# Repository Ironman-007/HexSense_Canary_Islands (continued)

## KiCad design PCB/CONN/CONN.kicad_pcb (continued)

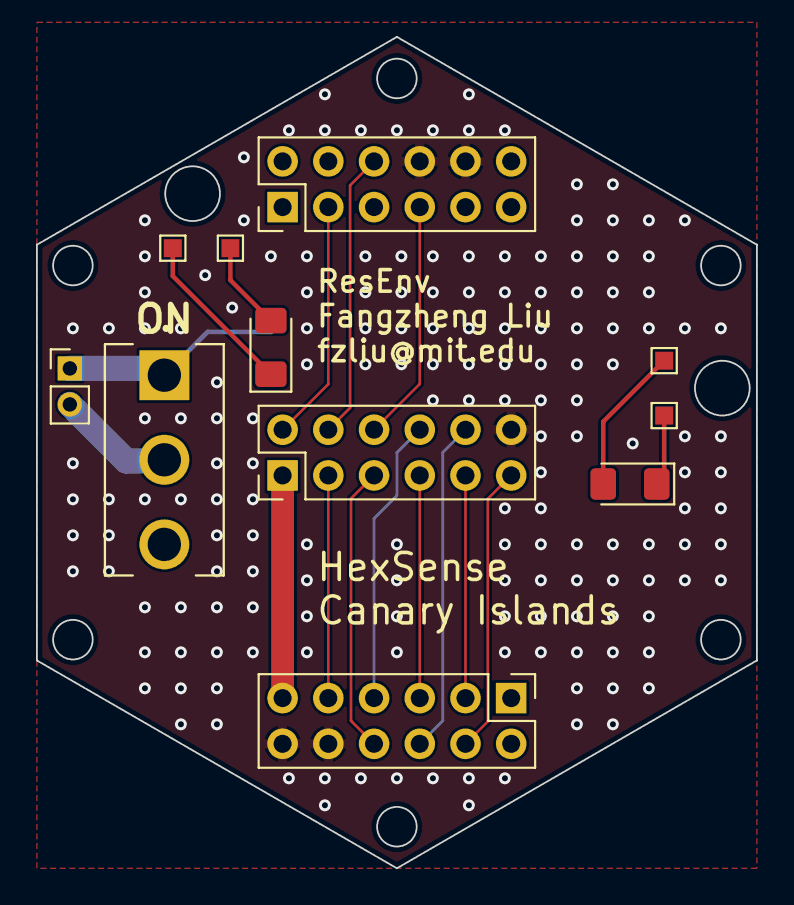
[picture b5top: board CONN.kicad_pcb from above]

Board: 2 copper layers, 40.0 x 46.2 mm, 12 parts (1 on the bottom side), 18 nets.

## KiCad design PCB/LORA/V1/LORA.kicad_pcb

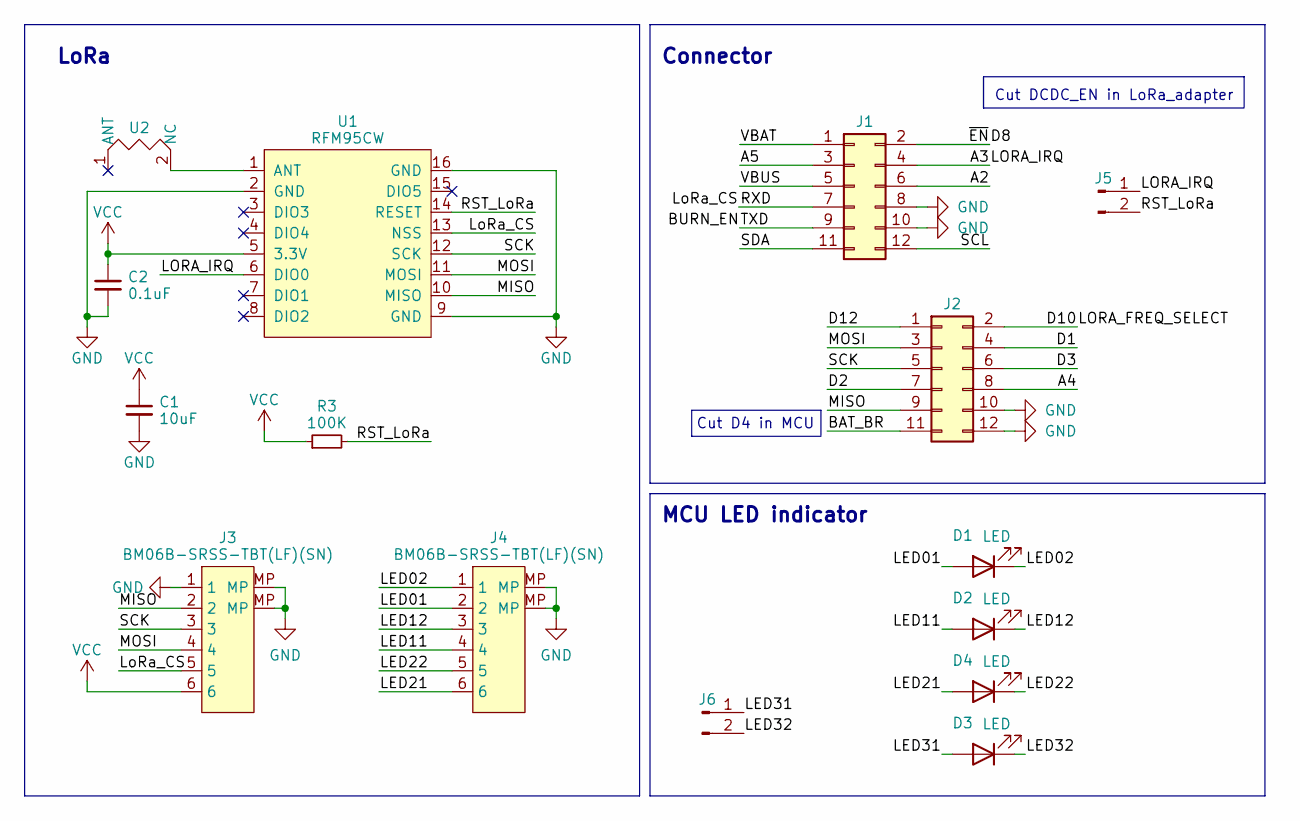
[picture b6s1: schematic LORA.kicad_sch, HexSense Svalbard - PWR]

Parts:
C1: 10uF; C_1206_3216Metric_Pad1.33x1.80mm_HandSolder
C2: 0.1uF; C_1206_3216Metric_Pad1.33x1.80mm_HandSolder
D1, D2, D3, D4: LED; LED_0603_1608Metric_Pad1.05x0.95mm_HandSolder
J1, J2: Conn_02x06_Odd_Even; PinHeader_2x06_P2.54mm_Vertical
J3, J4: BM06B-SRSS-TBT(LF)(SN); JST_SH_BM06B-SRSS-TB_1x06-1MP_P1.00mm_Vertical
J5, J6: Conn_01x02_Pin; PinHeader_1x02_P2.00mm_Vertical
R3: 100K; R_0603_1608Metric_Pad0.98x0.95mm_HandSolder
U1: RFM95CW; XCVR_RFM95W-915S2
U2: ANT-916-HESM

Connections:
/A2: J1.6
/A3: J1.4, J5.1, U1.6 (DIO0)
/A4: J2.8
/A5: J1.3
/BAT_BR: J2.11
/BURN_EN: J1.9
/D1: J2.4
/D2: J2.7
/D3: J2.6
/D8: J1.2
/D10: J2.2
/D12: J2.1
/LED01: D1.2 (A), J4.2
/LED02: D1.1 (K), J4.1
/LED11: D2.2 (A), J4.4
/LED12: D2.1 (K), J4.3
/LED21: D4.2 (A), J4.6
/LED22: D4.1 (K), J4.5
/LED31: D3.2 (A), J6.1
/LED32: D3.1 (K), J6.2
/LoRa_CS: J1.7, J3.5, U1.13 (NSS)
/MISO: J2.9, J3.2, U1.10 (MISO)
/MOSI: J2.3, J3.4, U1.11 (MOSI)
/RST_LoRa: J5.2, R3.2, U1.14 (RESET)
/SCK: J2.5, J3.3, U1.12 (SCK)
/SCL: J1.12
/SDA: J1.11
/VBAT: J1.1
/VBUS: J1.5
GND: C1.2, C2.2, J1.8, J1.10, J2.10, J2.12, J3.1, J3.MP, J4.MP, U1.2 (GND), U1.9 (GND), U1.16 (GND)
unnamed: U1.1 (ANT), U2.2 (NC)
VCC: C1.1, C2.1, J3.6, R3.1, U1.5 (3.3V)

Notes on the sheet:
Cut D4 in MCU
LoRa
Connector
MCU LED indicator
Cut DCDC_EN in LoRa_adapter

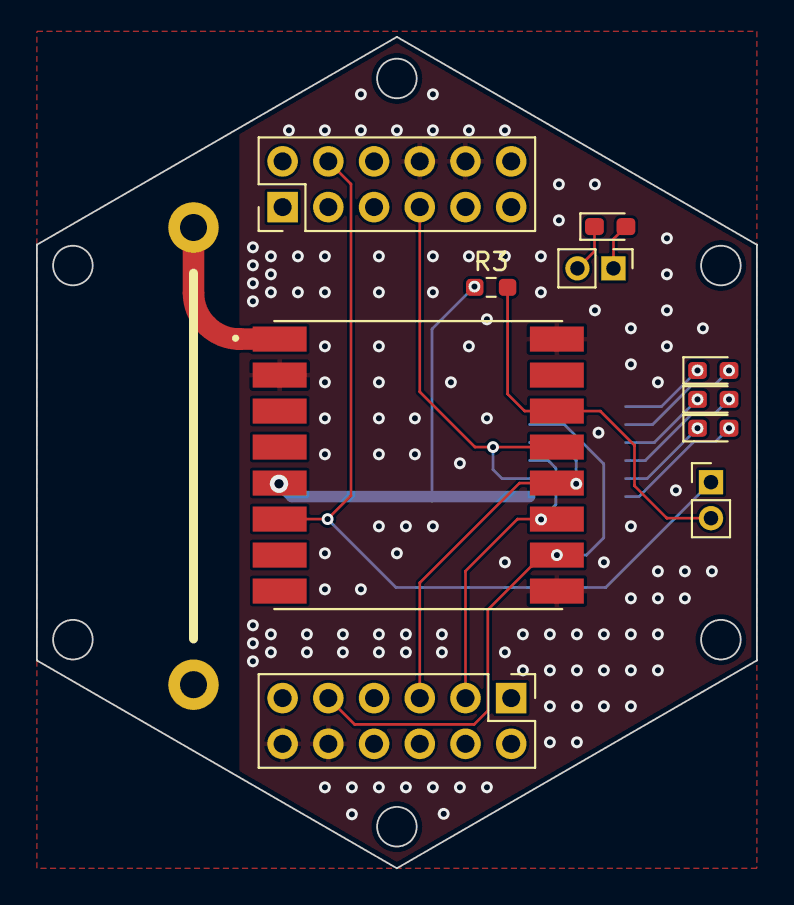
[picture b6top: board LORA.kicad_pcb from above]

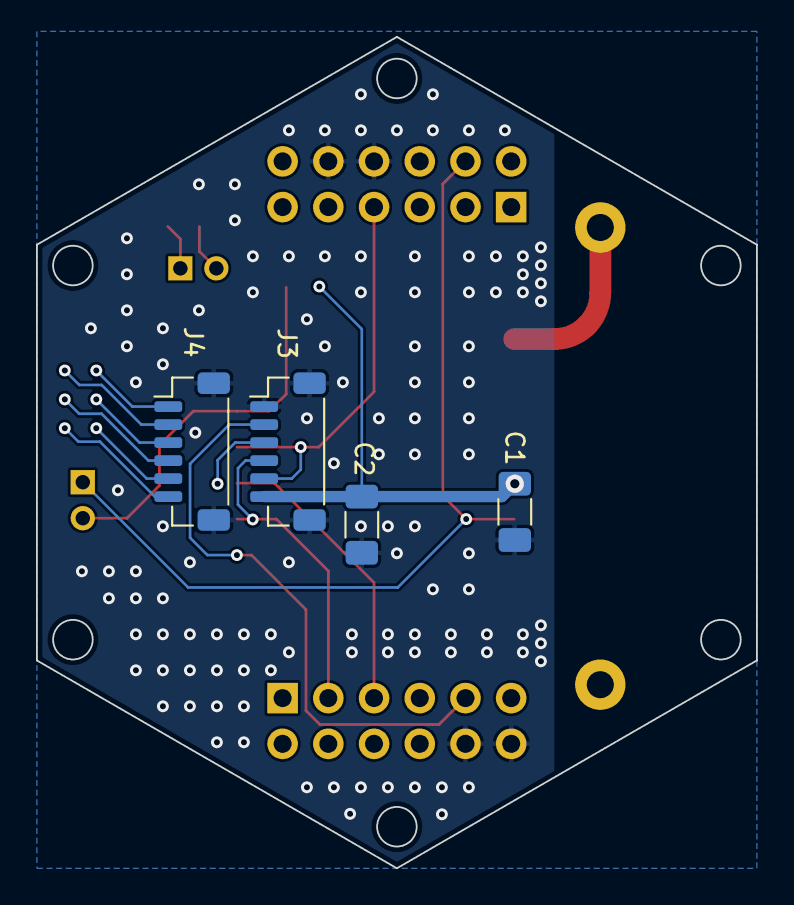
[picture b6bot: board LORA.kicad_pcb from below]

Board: 2 copper layers, 40.0 x 46.2 mm, 15 parts (4 on the bottom side), 17 nets.

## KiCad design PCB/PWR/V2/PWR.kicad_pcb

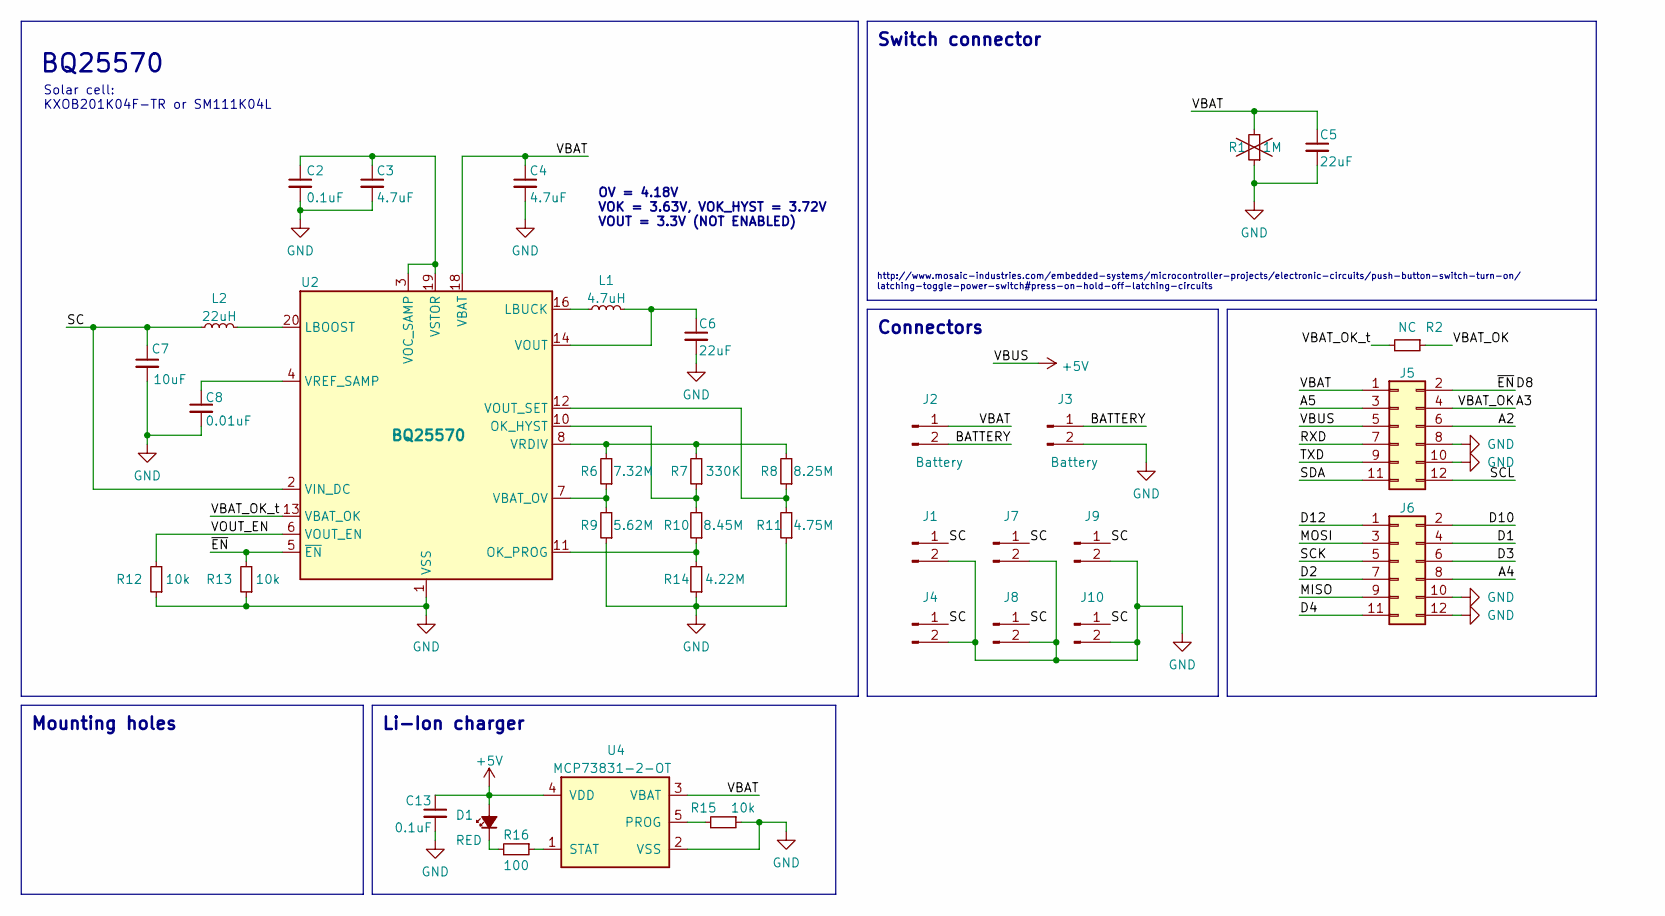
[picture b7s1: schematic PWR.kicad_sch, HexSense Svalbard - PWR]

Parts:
C2, C13: 0.1uF; C_0402_1005Metric_Pad0.74x0.62mm_HandSolder
C3, C4: 4.7uF; C_0603_1608Metric_Pad1.08x0.95mm_HandSolder
C5: 22uF; C_0603_1608Metric_Pad1.08x0.95mm_HandSolder
C6: 22uF; C_0805_2012Metric_Pad1.18x1.45mm_HandSolder
C7: 10uF; C_0603_1608Metric_Pad1.08x0.95mm_HandSolder
C8: 0.01uF; C_0402_1005Metric_Pad0.74x0.62mm_HandSolder
D1: RED; LED_0603_1608Metric_Pad1.05x0.95mm_HandSolder
J1, J4, J7, J8, J9, J10: Battery; Molex_Micro-Latch_53253-0270_1x02_P2.00mm_Vertical
J2, J3: Battery; PinHeader_2x01_P2.00mm_Vertical
J5, J6: Conn_02x06_Odd_Even; PinHeader_2x06_P2.54mm_Vertical
L1: 4.7uH; L_Wuerth_MAPI-3015
L2: 22uH; L_Taiyo-Yuden_NR-40xx_HandSoldering
R1: 1M; R_0603_1608Metric_Pad0.98x0.95mm_HandSolder
R2: NC; R_0603_1608Metric_Pad0.98x0.95mm_HandSolder
R6: 7.32M; R_0603_1608Metric_Pad0.98x0.95mm_HandSolder
R7: 330K; R_0603_1608Metric_Pad0.98x0.95mm_HandSolder
R8: 8.25M; R_0603_1608Metric_Pad0.98x0.95mm_HandSolder
R9: 5.62M; R_0603_1608Metric_Pad0.98x0.95mm_HandSolder
R10: 8.45M; R_0603_1608Metric_Pad0.98x0.95mm_HandSolder
R11: 4.75M; R_0603_1608Metric_Pad0.98x0.95mm_HandSolder
R12, R13, R15: 10k; R_0603_1608Metric_Pad0.98x0.95mm_HandSolder
R14: 4.22M; R_0603_1608Metric_Pad0.98x0.95mm_HandSolder
R16: 100; R_0603_1608Metric_Pad0.98x0.95mm_HandSolder
U2: BQ25570; QFN-20-1EP_3.5x3.5mm_P0.5mm_EP2x2mm
U4: MCP73831-2-OT; SOT-23-5

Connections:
+5V: C13.1, D1.2 (A), J5.5, U4.4 (VDD)
/A2: J5.6
/A3: J5.4, R2.1
/A4: J6.8
/A5: J5.3
/BATTERY: J2.2, J3.1
/D1: J6.4
/D2: J6.7
/D3: J6.6
/D4: J6.11
/D8: J5.2, R13.2, U2.5 (~EN)
/D10: J6.2
/D12: J6.1
/MISO: J6.9
/MOSI: J6.3
/RXD: J5.7
/SC: C7.1, J1.1, J4.1, J7.1, J8.1, J9.1, J10.1, L2.1, U2.2 (VIN_DC)
/SCK: J6.5
/SCL: J5.12
/SDA: J5.11
/TXD: J5.9
/VBAT: C4.1, C5.1, J2.1, J5.1, R1.2, U2.18 (VBAT), U4.3 (VBAT)
/VBAT_OK_t: R2.2, U2.13 (VBAT_OK)
/VOUT_EN: R12.2, U2.6 (VOUT_EN)
GND: C2.2, C3.2, C4.2, C5.2, C6.2, C7.2, C8.2, C13.2, J1.2, J3.2, J4.2, J5.8, J5.10, J6.10, J6.12, J7.2, J8.2, J9.2, J10.2, R1.1, R9.1, R11.1, R12.1, R13.1, R14.1, R15.1, U2.1 (VSS), U2.9 (VSS), U2.15 (VSS), U2.17 (VSS), U2.21 (VSS), U4.2 (VSS)
unnamed: D1.1 (K), R16.2
unnamed: L2.2, U2.20 (LBOOST)
unnamed: L1.1, U2.16 (LBUCK)
unnamed: R7.1, R10.2, U2.10 (OK_HYST)
unnamed: R10.1, R14.2, U2.11 (OK_PROG)
unnamed: R6.1, R9.2, U2.7 (VBAT_OV)
unnamed: C2.1, C3.1, U2.3 (VOC_SAMP), U2.19 (VSTOR)
unnamed: C6.1, L1.2, U2.14 (VOUT)
unnamed: R8.1, R11.2, U2.12 (VOUT_SET)
unnamed: R6.2, R7.2, R8.2, U2.8 (VRDIV)
unnamed: C8.1, U2.4 (VREF_SAMP)
unnamed: R15.2, U4.5 (PROG)
unnamed: R16.1, U4.1 (STAT)

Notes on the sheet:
Li-Ion charger
BQ25570
Switch connector
Mounting holes
Solar cell: KXOB201K04F-TR or SM111K04L
OV = 4.18V VOK = 3.63V, VOK_HYST = 3.72V VOUT = 3.3V (NOT ENABLED)
http://www.mosaic-industries.com/embedded-systems/microcontroller-projects/electronic-circuits/push-button-switch-turn-on/ latching-toggle-power-switch#press-on-hold-off-latching-circuits
Connectors

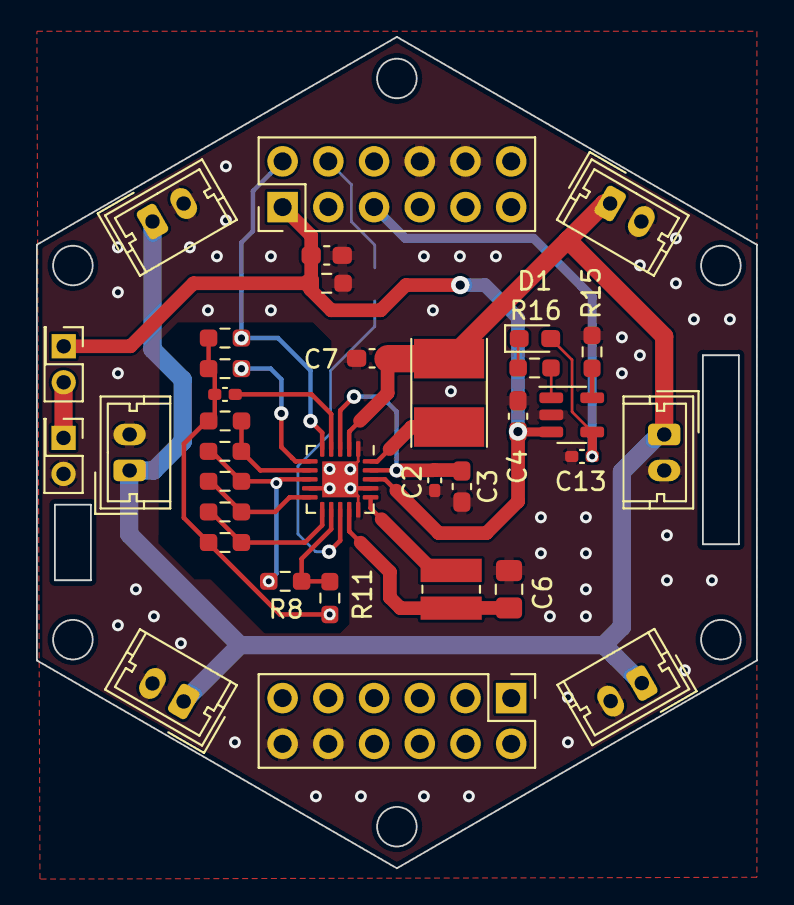
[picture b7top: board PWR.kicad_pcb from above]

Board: 2 copper layers, 40.0 x 46.2 mm, 36 parts (1 on the bottom side), 22 nets.

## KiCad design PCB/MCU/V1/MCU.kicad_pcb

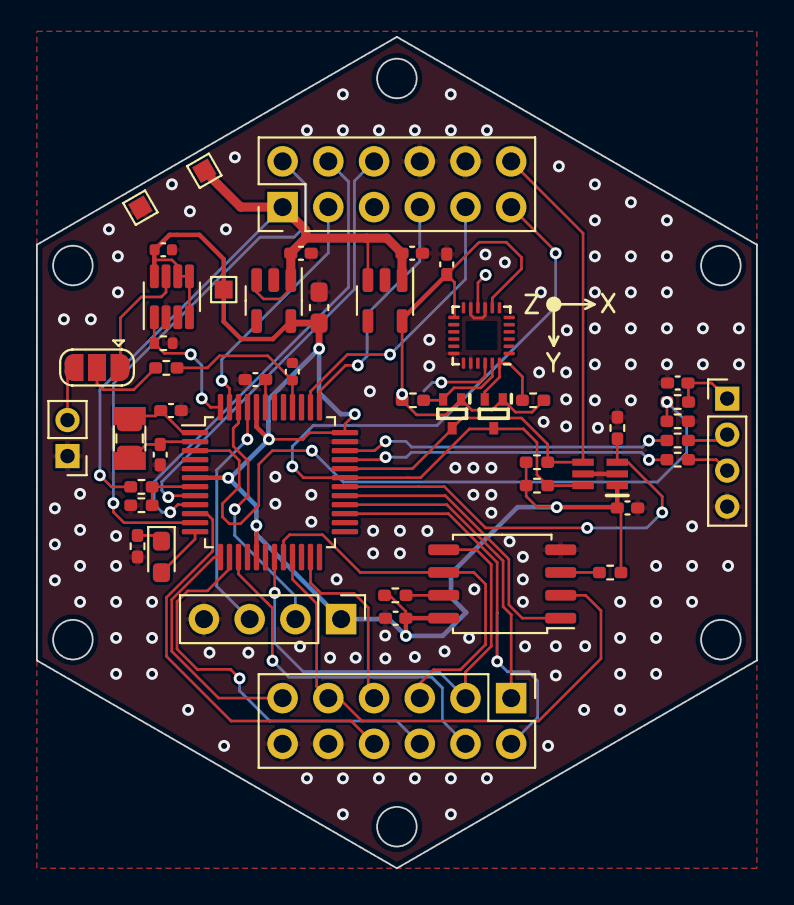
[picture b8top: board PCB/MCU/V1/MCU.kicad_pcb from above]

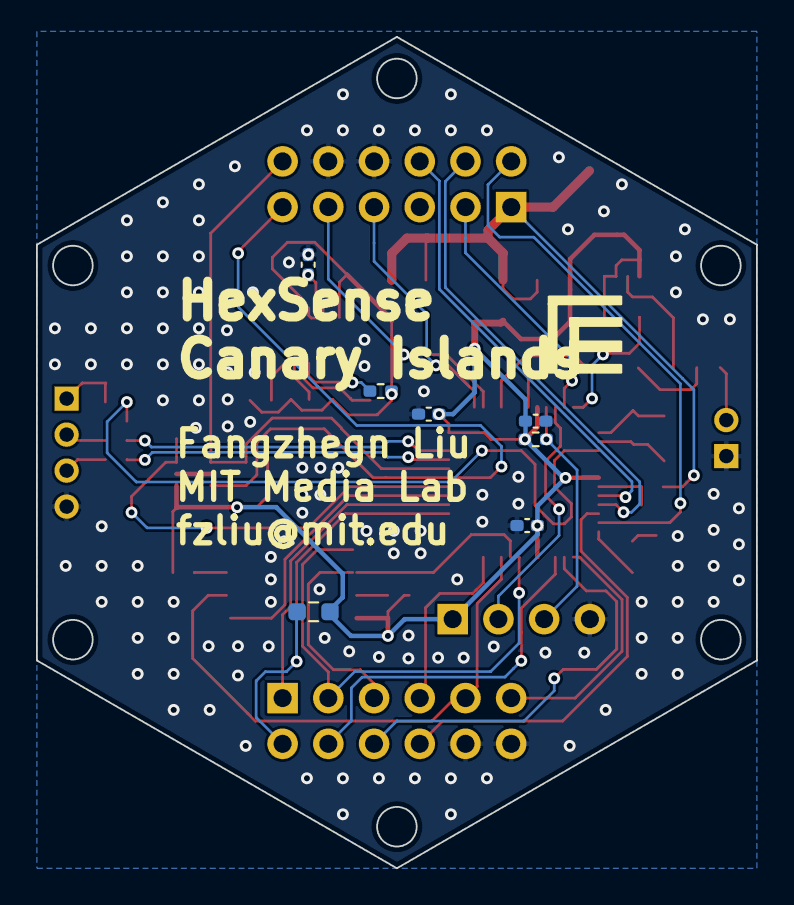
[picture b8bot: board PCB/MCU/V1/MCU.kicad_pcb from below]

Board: 2 copper layers, 40.0 x 46.2 mm, 56 parts (7 on the bottom side), 49 nets.

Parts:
C1, C3, C7: 0.01uF; C_0402_1005Metric_Pad0.74x0.62mm_HandSolder
C2, C4: 18pF; C_0402_1005Metric_Pad0.74x0.62mm_HandSolder
C5, C12: 1uF; C_0402_1005Metric_Pad0.74x0.62mm_HandSolder
C6, C8, C11, C14, C15, C16: 0.1uF; C_0402_1005Metric_Pad0.74x0.62mm_HandSolder
C9: 10uF; C_0603_1608Metric_Pad1.08x0.95mm_HandSolder
C10: 0.1uF; C_0402_1005Metric
C13: 10pF; C_0402_1005Metric
D1: RED; LED_0603_1608Metric_Pad1.05x0.95mm_HandSolder
IC2: LTC4311CSC6#TRPBF; SOT65P210X100-6N
J1, J2: Conn_02x06_Odd_Even; PinHeader_2x06_P2.54mm_Vertical
J4: Conn_01x04_Pin; PinHeader_1x04_P2.54mm_Vertical
J5: RESET; PinHeader_1x02_P2.00mm_Vertical
J6: Conn_01x04_Pin; PinHeader_1x04_P2.00mm_Vertical
JP1: RST Jumper; SolderJumper-3_P1.3mm_Open_RoundedPad1.0x1.5mm
Q1, Q2: PJE8408_R1_00001; SOTFL50P160X60-3N
R1, R2: 4.7K; R_0402_1005Metric_Pad0.72x0.64mm_HandSolder
R3, R12, R13, R17, R18, R21: 10K; R_0402_1005Metric_Pad0.72x0.64mm_HandSolder
R4: 10K; R_0402_1005Metric
R5, R6: 27; R_0402_1005Metric_Pad0.72x0.64mm_HandSolder
R7, R8, R14, R15: 499K; R_0402_1005Metric_Pad0.72x0.64mm_HandSolder
R9, R11: 330; R_0402_1005Metric_Pad0.72x0.64mm_HandSolder
R10: 10k; R_0402_1005Metric_Pad0.72x0.64mm_HandSolder
R19: PH; R_0805_2012Metric_Pad1.20x1.40mm_HandSolder
R20: 10K; R_0603_1608Metric_Pad0.98x0.95mm_HandSolder
TP1, TP2, TP3: BAT_TP; TestPoint_Pad_1.0x1.0mm
U1: MB85RS2MTAPNF-G-BDERE1; SSOP-8_5.25x5.24mm_P1.27mm
U2: ATSAMD21G18A-A; TQFP-48_7x7mm_P0.5mm
U3: MAX6372; SOT-23-8
U4: ADP160AUJZ-3.3-R7; TSOT-23-5
U5: ICM-20948; InvenSense_QFN-24_3x3mm_P0.4mm
U6: ADP160AUJZ-1.8; TSOT-23-5
Y1: 32KHz; Crystal_SMD_3215-2Pin_3.2x1.5mm

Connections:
+1V8: C11.1, Q1.1, Q2.1, R17.2, R18.2, R21.2, U5.8 (VDDIO), U5.13 (VDD), U6.5 (VOUT)
+5V: C7.1, J6.1, R14.1
/A0: R14.2, R15.1, U2.3 (PA02)
/A1: R7.2, R8.1, U2.7 (PB08)
/A2: J1.6, U2.8 (PB09)
/A3: J1.4, U2.9 (PA04)
/A4: J2.8, U2.10 (PA05)
/A5: J1.3, U2.47 (PB02)
/D1: J2.4, U2.15 (PA10)
/D2: J2.7, U2.23 (PA14)
/D3: J2.6, U2.14 (PA09)
/D4: J2.11, U2.13 (PA08)
/D6: U1.1 (~CS), U2.29 (PA20)
/D7: IC2.3 (ENABLE), R3.2, U2.30 (PA21)
/D8: J1.2, U2.11 (PA06)
/D9: D1.2 (A), U2.12 (PA07)
/D10: J2.2, R20.2, U2.27 (PA18)
/D12: J2.1, U2.28 (PA19)
/MISO: J2.9, U1.2 (SO), U2.21 (PA12)
/MOSI: J2.3, U1.5 (SI), U2.19 (PB10)
/RXD: J1.7, U2.37 (PB22)
/RXLED: R4.1, U2.48 (PB03), U3.1 (WDI)
/SCK: J2.5, U1.6 (SCK), U2.20 (PB11)
/SCL: IC2.4 (BUS2), J1.12, Q2.3, R1.1, U2.32 (PA23)
/SCL_1V8: Q2.2, R17.1, U5.23 (SCL/SCLK)
/SDA: IC2.6 (BUS1), J1.11, Q1.3, R2.1, U2.31 (PA22)
/SDA_1V8: Q1.2, R18.1, U5.24 (SDA/SDI)
/SWDCLK: J4.3, R10.1, U2.45 (PA30)
/SWDIO: J4.2, U2.46 (PA31)
/TXD: J1.9, U2.38 (PB23)
/USB+: R5.1, U2.34 (PA25)
/USB-: R6.1, U2.33 (PA24)
/VBAT: C8.1, C14.1, J1.1, R7.1, TP3.1, U4.1 (VIN), U4.3 (EN), U6.1 (VIN), U6.3 (EN)
/~RESET: C13.1, R9.2, U2.40 (~RESET)
GND: C1.2, C2.1, C3.2, C4.1, C5.1, C6.1, C7.2, C8.2, C9.1, C10.2, C11.2, C12.1, C13.2, C14.2, C15.1, C16.2, IC2.2 (GND_1), IC2.5 (GND_2), J1.8, J1.10, J2.10, J2.12, J4.4, J5.1, J6.4, R3.1, R4.2, R8.2, R11.2, R15.2, TP2.1, U1.4 (GND), U2.5 (GNDANA), U2.18 (GND), U2.35 (GND), U2.42 (GND), U3.2 (GND), U4.2 (GND), U5.9 (AD0/SDO), U5.11 (FSYNC), U5.18 (GND), U5.20 (RESV_20), U6.2 (GND)
unnamed: D1.1 (K), R11.1
unnamed: J5.2, JP1.3 (B)
unnamed: J6.2, R5.2
unnamed: J6.3, R6.2
unnamed: JP1.1 (A), U3.7 (~WDO)
unnamed: JP1.2 (C), R9.1
unnamed: R12.1, U1.7 (~HOLD)
unnamed: R13.1, U1.3 (~WP)
unnamed: C2.2, R19.2, U2.1 (PA00), Y1.2
unnamed: C4.2, R19.1, U2.2 (PA01), Y1.1
unnamed: C12.2, U2.43 (VDDCORE)
unnamed: C16.1, U5.10 (REGOUT)
unnamed: R21.1, U5.22 (~CS)
VCC: C1.1, C3.1, C5.2, C6.2, C9.2, C10.1, C15.2, IC2.1 (VCC), J4.1, R1.2, R2.2, R10.2, R12.2, R13.2, R20.1, TP1.1, U1.8 (VDD), U2.6 (VDDANA), U2.17 (VDDIO), U2.36 (VDDIO), U2.44 (VDDIN), U3.4 (SET0), U3.5 (SET1), U3.6 (SET2), U3.8 (VCC), U4.5 (VOUT)

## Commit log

2023-11-22 udated by FZ
2024-02-05 auto stand work
2024-02-05 auto stand work & lora work
2024-02-05 added ArduCAM_Mega_API_tst
2024-02-06 ArduCAM_Mega_API_tst working
2024-02-06 ArduCAM_Mega_API_tst working well. needs to take picture multiple times
2024-02-06 Added AstroAnt firmware
2024-02-08 Added LoRa feq selection, both are working
2024-02-09 Add MLX90640 tst for AstroAnt
2024-02-09 Ant BLE working
2024-02-10 Ant IMU cali working
2024-02-10 Ant tracking works
2024-02-10 Ant IR works, need to set value to the repeated field
2024-02-10 Ant working, Ant_Canary_Tracking_IR
2024-02-12 Added Central firmware for Ant
2024-02-12 Ant Central works
2024-02-12 Updated ant proto file
2024-02-13 use repeated field for the Ant
2024-02-14 working on the camera firmware
2024-02-16 camera power on working
2024-02-17 CAM_HEXSENSE_CANARY_V1 take photo, store FRAM, and read from FRAM works
2024-02-17 CAM_HEXSENSE_CANARY_V1 two cameras working together
2024-02-17 CAM_HEXSENSE_CANARY_V1 photo quality is better
2024-02-17 CAM_HEXSENSE_CANARY_V1 all cameras working
2024-02-18 added CAM_HEXSENSE_CANARY_V2
2025-03-31 pc:working on stm32l476 mcu board
2025-04-01 mac:working on the stm32l476 mcu board
2025-04-01 mac: finishing the L476 mcu board
2025-04-01 pc:finished L476 MCU board
2025-04-01 mac: finishing the L476 mcu board design rule checking
2025-04-01 mac: added esp32s3 mcu brd
2025-04-02 mac:working on esp32s3 mcu brd, forgot the strapping pins.
